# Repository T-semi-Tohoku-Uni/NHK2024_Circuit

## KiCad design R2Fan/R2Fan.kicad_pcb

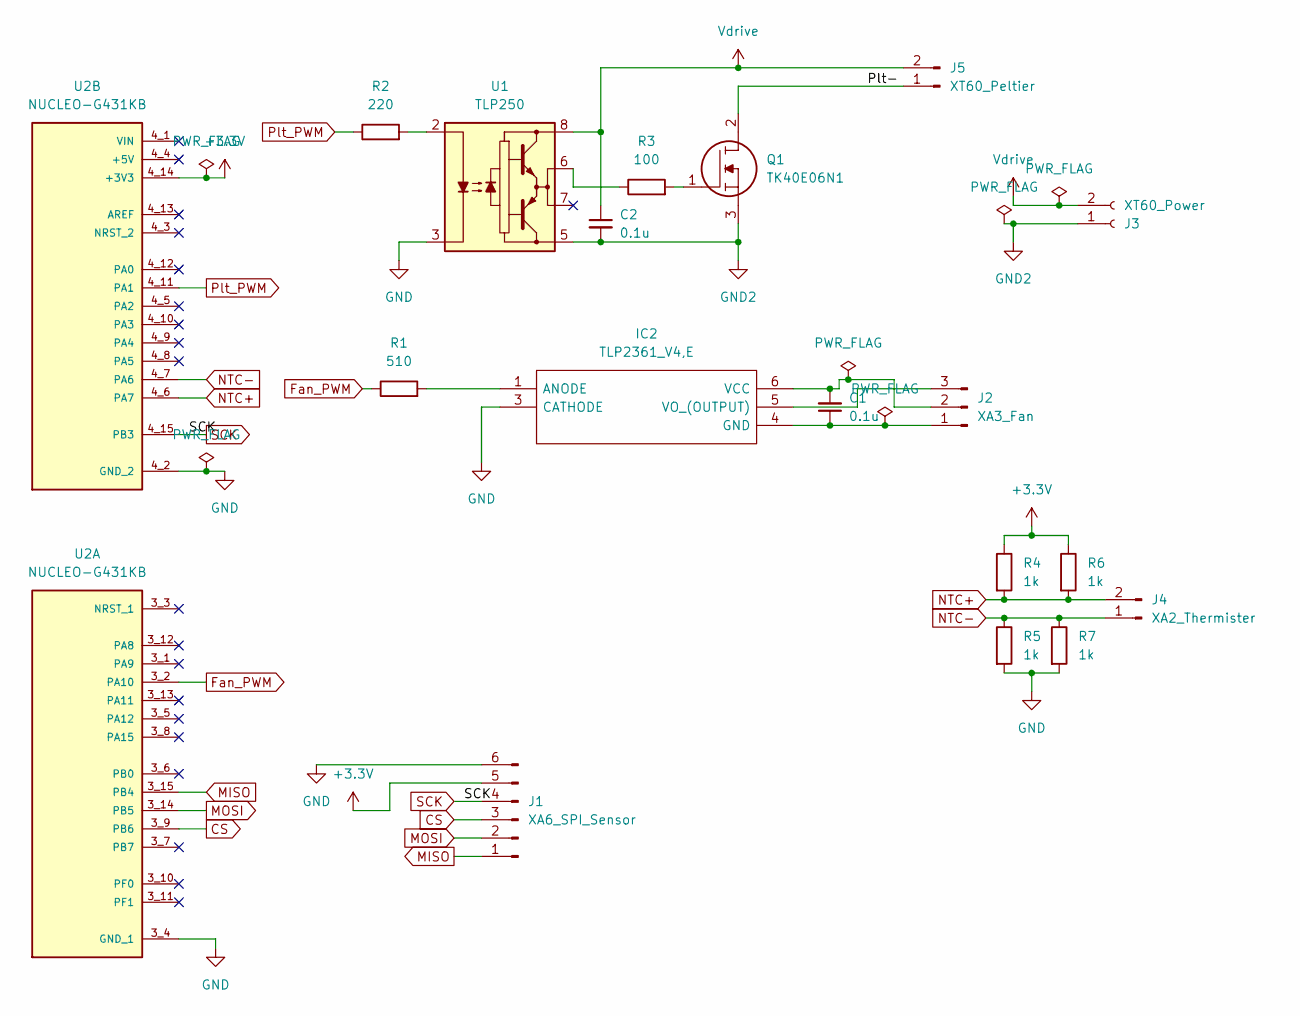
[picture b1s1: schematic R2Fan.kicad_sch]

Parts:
C1, C2: 0.1u; C_0603_1608Metric
IC2: TLP2361_V4,E; MFSOP6-5_4.4x3.6mm_P1.27mm; Manufacturer_Part_Number TLP2361(V4,E; Mouser Part Number 757-TLP2361V4E
J1: XA6_SPI_Sensor; JST_XA_S06B-XASK-1_1x06_P2.50mm_Horizontal
J2: XA3_Fan; JST_XA_S03B-XASK-1_1x03_P2.50mm_Horizontal
J3: XT60_Power; AMASS_XT60PW-M_1x02_P7.20mm_Horizontal
J4: XA2_Thermister; JST_XA_S02B-XASK-1_1x02_P2.50mm_Horizontal
J5: XT60_Peltier; AMASS_XT60PW-F_1x02_P7.20mm_Horizontal
Q1: TK40E06N1; TO-220-3_Horizontal_TabDown; Manufacturer_Part_Number TK40E06N1; Mouser Part Number N/A
R1: 510; R_0603_1608Metric
R2: 220; R_0603_1608Metric
R3: 100; R_0603_1608Metric
R4, R5, R6, R7: 1k; R_0603_1608Metric
U1: TLP250; DIP-8_W7.62mm
U2: NUCLEO-G431KB; MODULE_NUCLEO-G431KBT6; PARTREV 3; DigiKey_Part_Number 497-19489-ND

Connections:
+3.3V: J1.5, R4.1, R6.1, U2.4_14 (+3V3)
/Plt-: J5.1, Q1.2
CS: J1.3, U2.3_9 (PB6)
Fan_PWM: R1.1, U2.3_2 (PA10)
GND: IC2.3 (CATHODE), J1.6, R5.2, R7.2, U1.3 (C), U2.3_4 (GND_1), U2.4_2 (GND_2)
GND2: C2.2, J3.1, Q1.3, U1.5 (VEE)
MISO: J1.1, U2.3_15 (PB4)
MOSI: J1.2, U2.3_14 (PB5)
NTC+: J4.2, R4.2, R6.2, U2.4_6 (PA7)
NTC-: J4.1, R5.1, R7.1, U2.4_7 (PA6)
unnamed: IC2.1 (ANODE), R1.2
unnamed: C1.1, IC2.4 (GND), J2.1
unnamed: C1.2, IC2.6 (VCC), J2.2
unnamed: IC2.5 (VO_(OUTPUT)), J2.3
unnamed: Q1.1, R3.2
unnamed: R3.1, U1.6 (VO)
unnamed: R2.2, U1.2 (A)
Plt_PWM: R2.1, U2.4_11 (PA1)
SCK: J1.4, U2.4_15 (PB3)
Vdrive: C2.1, J3.2, J5.2, U1.8 (VCC)

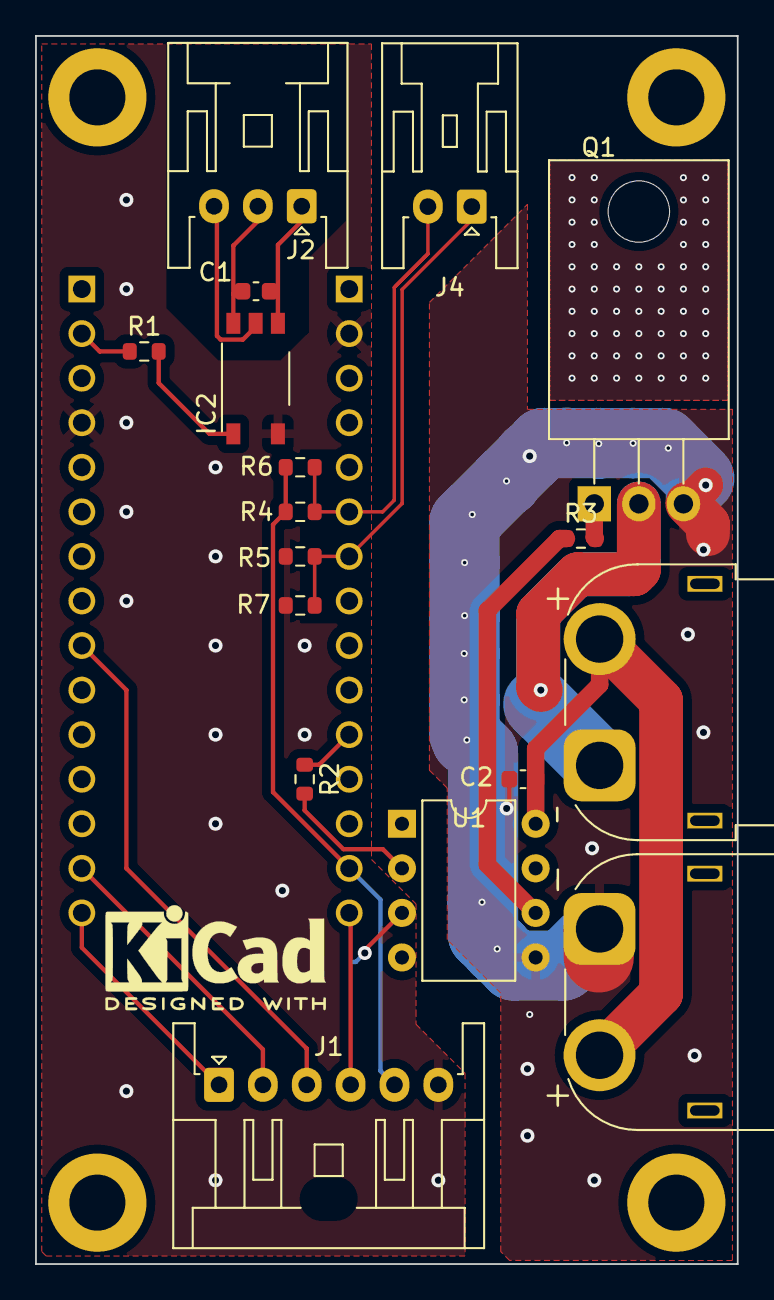
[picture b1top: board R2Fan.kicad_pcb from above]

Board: 2 copper layers, 40.0 x 70.0 mm, 18 parts (0 on the bottom side), 20 nets.

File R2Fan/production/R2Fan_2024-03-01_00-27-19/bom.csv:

Designator,Footprint,Quantity,Value,LCSC Part #
"C1, C2",0603,2,0.1u,
IC2,MFSOP6-5_4.4x3.6mm_P1.27mm,1,"TLP2361_V4,E",
J1,JST_XA_S06B-XASK-1_1x06_P2.50mm_Horizontal,1,XA6_SPI_Sensor,
J2,JST_XA_S03B-XASK-1_1x03_P2.50mm_Horizontal,1,XA3_Fan,
J3,AMASS_XT60PW-M_1x02_P7.20mm_Horizontal,1,XT60_Power,
J4,JST_XA_S02B-XASK-1_1x02_P2.50mm_Horizontal,1,XA2_Thermister,
J5,AMASS_XT60PW-F_1x02_P7.20mm_Horizontal,1,XT60_Peltier,
Q1,TO-220-3_Horizontal_TabDown,1,TK40E06N1,
R1,0603,1,510,
R2,0603,1,220,
R3,0603,1,100,
"R4, R5, R6, R7",0603,4,1k,
U1,DIP-8_W7.62mm,1,TLP250,
U2,MODULE_NUCLEO-G431KBT6,1,NUCLEO-G431KB,

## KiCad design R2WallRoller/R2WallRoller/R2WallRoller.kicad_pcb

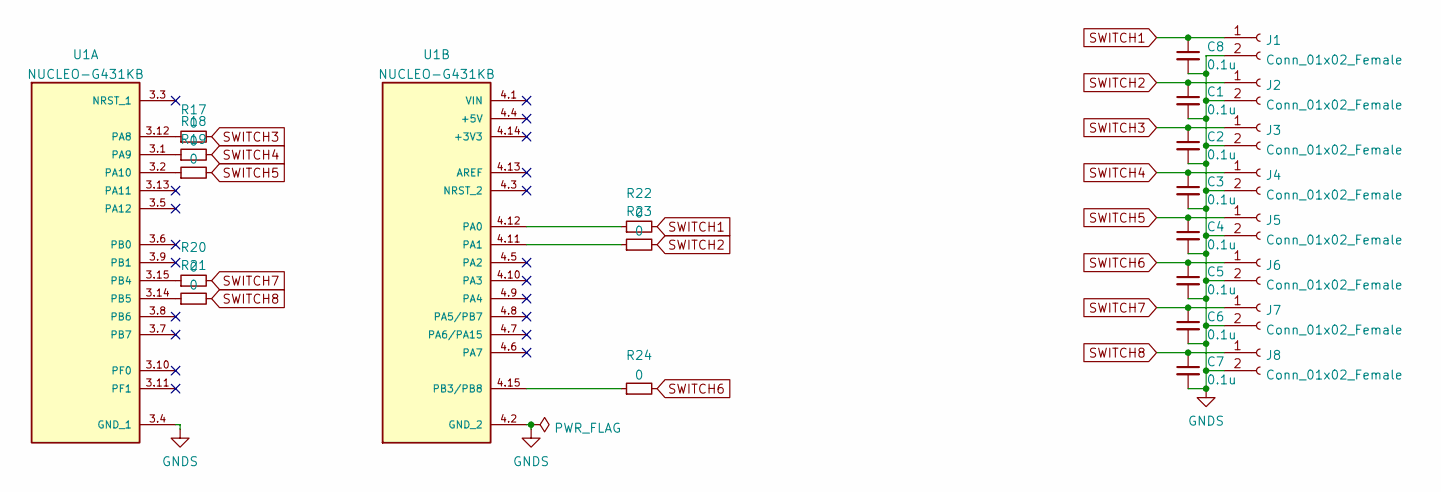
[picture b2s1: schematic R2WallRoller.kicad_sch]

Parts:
C1, C2, C3, C4, C5, C6, C7, C8: 0.1u; C_0603_1608Metric
J1, J2, J3, J4, J5, J6, J7, J8: Conn_01x02_Female; JST_XA_S02B-XASK-1_1x02_P2.50mm_Horizontal
R17, R18, R19, R20, R21, R22, R23, R24: 0; R_0603_1608Metric
U1: NUCLEO-G431KB; MODULE_NUCLEO-G431; PARTREV 5

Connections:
GNDS: C1.2, C2.2, C3.2, C4.2, C5.2, C6.2, C7.2, C8.2, J1.2, J2.2, J3.2, J4.2, J5.2, J6.2, J7.2, J8.2, U1.3.4 (GND_1), U1.4.2 (GND_2)
unnamed: R17.1, U1.3.12 (PA8)
unnamed: R18.1, U1.3.1 (PA9)
unnamed: R19.1, U1.3.2 (PA10)
unnamed: R20.1, U1.3.15 (PB4)
unnamed: R21.1, U1.3.14 (PB5)
unnamed: R22.1, U1.4.12 (PA0)
unnamed: R23.1, U1.4.11 (PA1)
unnamed: R24.1, U1.4.15 (PB3/PB8)
SWITCH1: C8.1, J1.1, R22.2
SWITCH2: C1.1, J2.1, R23.2
SWITCH3: C2.1, J3.1, R17.2
SWITCH4: C3.1, J4.1, R18.2
SWITCH5: C4.1, J5.1, R19.2
SWITCH6: C5.1, J6.1, R24.2
SWITCH7: C6.1, J7.1, R20.2
SWITCH8: C7.1, J8.1, R21.2

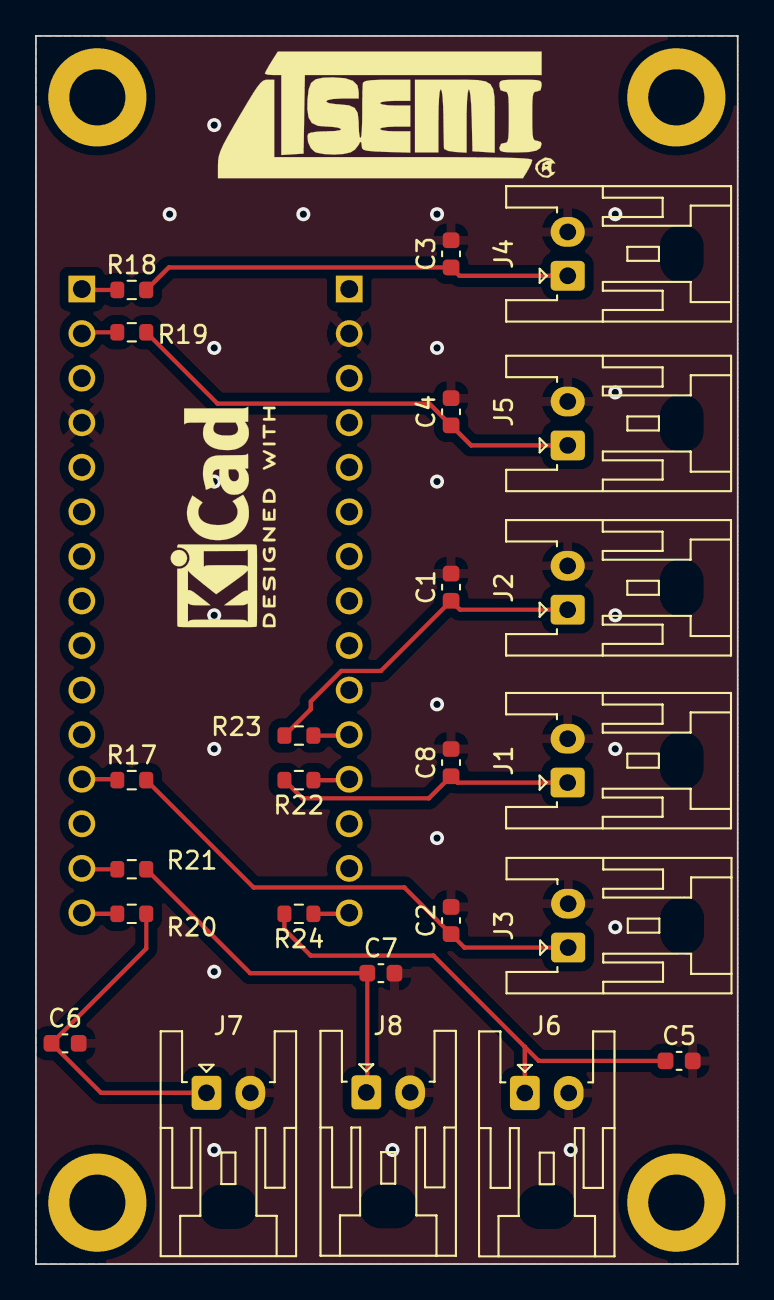
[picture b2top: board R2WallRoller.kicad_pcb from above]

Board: 2 copper layers, 40.0 x 70.0 mm, 25 parts (0 on the bottom side), 17 nets.

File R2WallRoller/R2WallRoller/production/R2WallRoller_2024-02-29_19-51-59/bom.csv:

Designator,Footprint,Quantity,Value,LCSC Part #
"C1, C2, C3, C4, C5, C6, C7, C8",0603,8,0.1u,
"J1, J2, J3, J4, J5, J6, J7, J8",JST_XA_S02B-XASK-1_1x02_P2.50mm_Horizontal,8,Conn_01x02_Female,
"R17, R18, R19, R20, R21, R22, R23, R24",0603,8,0,
U1,MODULE_NUCLEO-G431,1,NUCLEO-G431KB,

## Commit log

2024-02-28 for Hirayama Check
2024-02-29 add R2WallRoller
2024-02-29 order ver on 20240301
